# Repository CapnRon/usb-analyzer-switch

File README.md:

Included are the source kicad files, as well as a set of gerbers. minimum hole diameter on the microvias on the usb-c port is 0.25mm 

The switch connects to TP1 and TP2, it is of the SPST(single pole, single throw) variety from ali-express, but any SPST switch should do the job. Links to some examples that can work are included below:
```
https://www.aliexpress.us/item/3256804718359582.html
https://www.aliexpress.us/item/3256804642765727.html
https://www.aliexpress.us/item/3256805086884883.html
```

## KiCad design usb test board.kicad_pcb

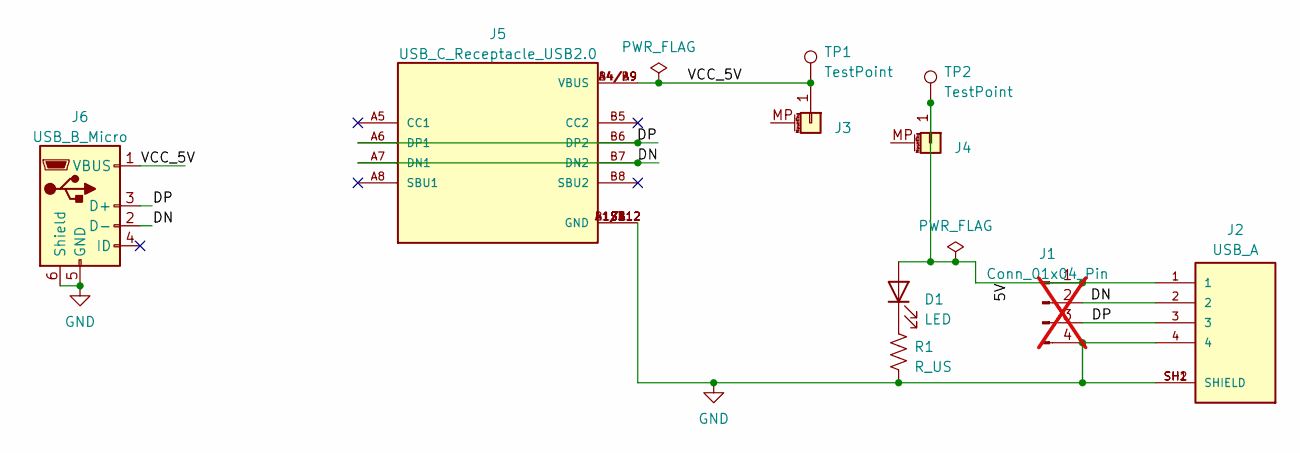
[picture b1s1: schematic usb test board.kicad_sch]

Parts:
D1: LED; LED_1206_3216Metric_Pad1.42x1.75mm_HandSolder
J1: Conn_01x04_Pin; PinHeader_1x04_P2.54mm_Vertical; not fitted
J2: USB_A; CUI_UJ2-AH-4-SMT; PART_REV 1.01
J3, J4: Conn_01x01_MountingPin; Pin_D1.0mm_L10.0mm
J5: USB_C_Receptacle_USB2.0; GCT_USB4110GFA; PARTREV A; DigiKey_Part_Number 2073-USB4135-GF-ATR-ND
J6: USB_B_Micro; USB_Micro-B_GCT_USB3076-30-A
R1: R_US; R_1206_3216Metric_Pad1.30x1.75mm_HandSolder
TP1, TP2: TestPoint; TestPoint_Pad_4.0x4.0mm

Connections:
/5V: D1.2 (A), J1.1, J2.1, J4.1, TP2.1
/DN: J1.2, J2.2, J5.A7 (DN1), J5.B7 (DN2), J6.2 (D-)
/DP: J1.3, J2.3, J5.A6 (DP1), J5.B6 (DP2), J6.3 (D+)
/VCC_5V: J3.1, J5.A4/B9 (VBUS), J5.B4/A9 (VBUS), J6.1 (VBUS), TP1.1
GND: J1.4, J2.4, J2.SH1 (SHIELD), J2.SH2 (SHIELD), J5.A1/B12 (GND), J5.B1/A12 (GND), J5.S1 (GND), J5.S2 (GND), J5.S3 (GND), J5.S4 (GND), J6.5 (GND), J6.6 (Shield), R1.1
unnamed: D1.1 (K), R1.2

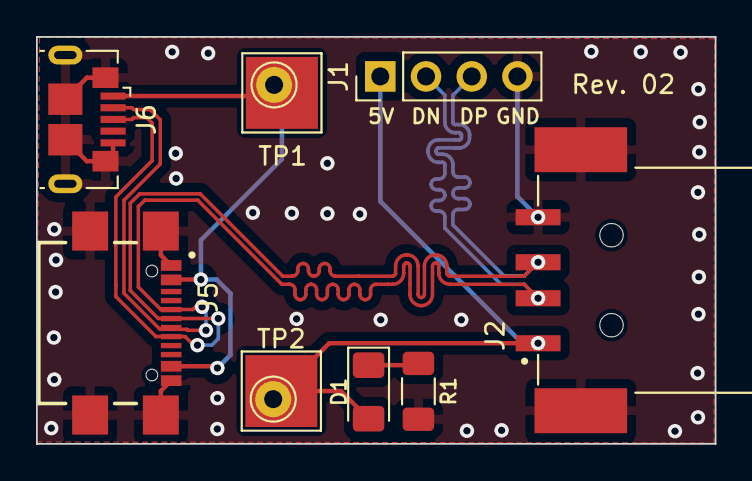
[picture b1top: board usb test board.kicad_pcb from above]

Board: 2 copper layers, 37.7 x 22.6 mm, 10 parts (0 on the bottom side), 6 nets.

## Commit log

2024-01-17 Create README.md
    first commit
2024-01-17 Update highspeed USB differential traces
    Update highspeed USB differential traces, added 0.25mm hole size microvias in the usb-c connector
2024-01-17 Update README.md
    Added links to order switches
2024-01-17 Update README.md
    Added 3D renders of the board
2024-02-10 correct usb-a data pin polarity
2024-02-10 added gerbers
2024-02-20 add revision to top silk, clean up
2024-02-20 adjust usb connector labels
2024-02-20 Improved usb vias for easier manufacturing
2024-02-20 improved differential pair
